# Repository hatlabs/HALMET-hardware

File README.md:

# Hat Labs Marine Engine/Tank Interface

This repository contains the Hat Labs Marine Engine/Tank Interface (HALMET) hardware design. HALMET is a powerful microcontroller development board designed for marine environments with a focus on engine and tank monitoring.

HALMET can be used to easily create different types of sensors and control devices for boats. Use scenarios include:

- RPM sensors
- tank level sensors
- bilge sensors
- Engine alarm sensors
- Engine temperature sensors

Since the board has native WiFi and NMEA 2000 compatible CAN bus connectivity, it can be used to create boards with either Signal K or native NMEA 2000 connectivity (or both!).

## Features

The main design features include:

- Built around ESP32, a powerful 32-bit microcontroller with 4 MB of flash
- Wide-range 6-32 V power input with surge protection
- NMEA 2000 compatible CAN interface (4-pin pluggable terminal block screw connector)
- 4 analog inputs with 0-32V input range and 16-bit resolution (2-pin pluggable terminal block screw connectors)
- 4 digital inputs with -32-32V input range, Schmitt triggered logic level threshold at 1.5V (2-pin pluggable terminal block screw connectors)
- 1-Wire interface (3-pin 2.54 mm header)
- I2C interface with both a SparkFun Qwiic connector and a 4-pin 2.54 mm header
- USB interface for programming and serial communication (USB Micro B)
- All above interfaces with proper electromagnetic compatibilty (EMC) design -- the device won't interfere with navigational devices or radio equipment
- All available general-purpose input/output (GPIO) pins broken out to a separate header
- Board designed to fit low-cost waterproof 100x68x50 mm enclosures

Rendering of a version 1.0.0 board:

<!--
Front side.

Back side.

-->

## Getting HALMET

HALMET will be available for purchase at the [Hat Labs web store](https://shop.hatlabs.fi/).

## Documentation

HALMET documentation will be available at the [project GitHub Pages](https://docs.hatlabs.fi/halmet/).

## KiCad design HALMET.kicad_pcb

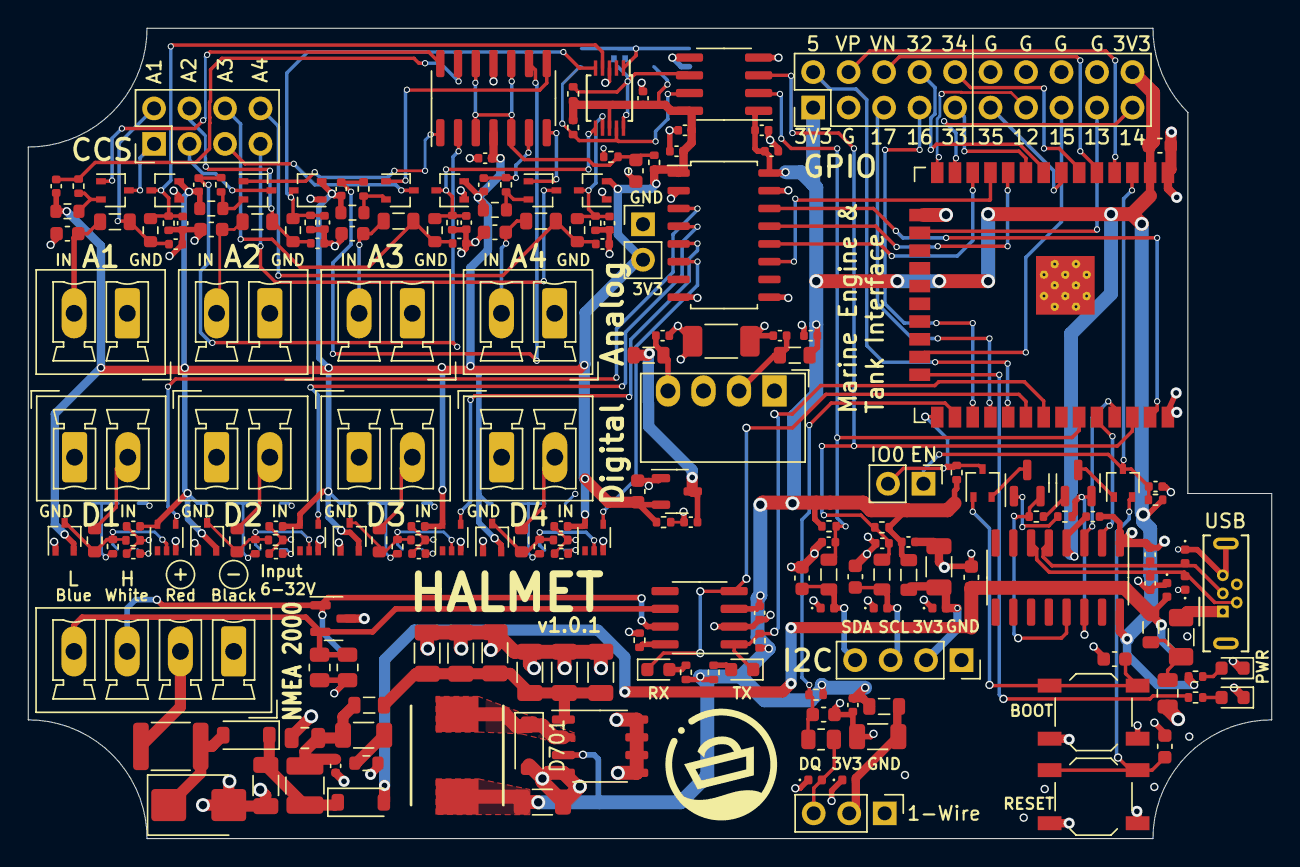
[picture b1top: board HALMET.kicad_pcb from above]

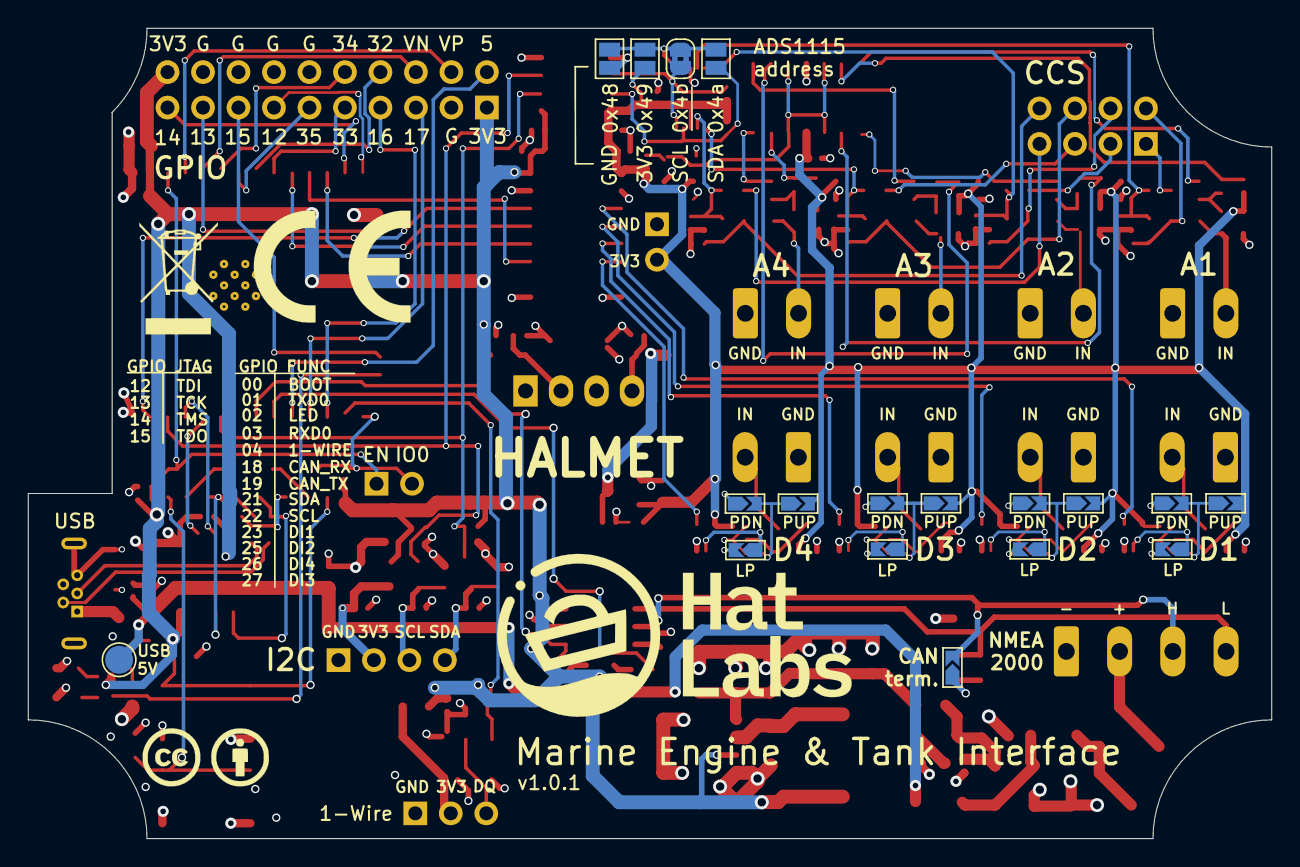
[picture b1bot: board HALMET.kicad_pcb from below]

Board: 4 copper layers, 89.0 x 58.0 mm, 222 parts (21 on the bottom side), 119 nets.

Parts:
C202: 22uF; C_0603_1608Metric
C203: 1uF; C_0402_1005Metric
C304: 47uF/6.3V; C_1206_3216Metric
C402: 4.7uF/16V; C_0603_1608Metric
C403, C404: 10pF/50V; C_0402_1005Metric
C501, C502: 100nF/50V; C_0603_1608Metric
C503, C715: 1uF/50V; C_0805_2012Metric
C601, C604, C612, C614, C705, C706: 33pF/50V; C_0603_1608Metric
C602, C606, C607, C608, C609, C610, C624, C901, C1113, C1114, C1115, C1116, C1204, C1205, C1206, C1207: 100nF; C_0402_1005Metric
C603, C605, C613, C615, C702, C703: 33pF; C_0402_1005Metric
C611: 68nF; C_0603_1608Metric
C620, C621, C622, C623: 10nF; C_0402_1005Metric
C701, C801: 10uF; C_0402_1005Metric
C704, C707, C708, C709, C710, C711, C712, C714, C803: 10uF/50V; C_1206_3216Metric
C713: 4.7nF/50V; C_0402_1005Metric
C716: 4.7uF/50V; C_1206_3216Metric
C802: 1nF/50V; C_0603_1608Metric
C1101, C1102, C1103, C1112: 3.3nF; C_0402_1005Metric
C1104, C1105, C1106, C1107: 220pF; R_0402_1005Metric
C1201, C1202, C1208, C1210: 4.7uF; C_0402_1005Metric
C1203: 10uF/10V; C_0603_1608Metric
C1209: 220pF/2kV; C_1808_4520Metric
D201, D303, D701: B5819W; D_SOD-123
D301: SMBJ33CA; D_SMB
D401, D402, D403, D503, D504, D903, D904, D905: ESD5451N; D_0402_1005Metric
D501: BLUE LED; LED_0603_1608Metric
D502: RED LED; LED_0603_1608Metric
D603, D604, D605, D611, D1103, D1104, D1105, D1113: BAT54S; SOT-323_SC-70
D801: SM24CANB; SOT-23
D1001, D1002: GREEN LED; LED_0603_1608Metric
D1101, D1102: BAT54A; SOT-323_SC-70
F301: mSMD050-60V; Fuse_1812_4532Metric
F401: BSMD1206-100-6V; Fuse_1206_3216Metric
FB401, FB701, FB704, FB801: GZ2012D601TF; L_0805_2012Metric
FB601, FB602, FB603, FB604, FB702, FB703: GZ2012D101TF; L_0805_2012Metric
G601: CC-BY; cc-by_5mm
G602: CE-logo; CE-Logo_11.2x8mm_SilkScreen
G605: HL-Logo; Hat_Labs_25.4mm
G701: HL-Pictogram; HaL_picto_8mm
H1001, H1002: MountingHole; MountingSlot_3.2mm_M3_Unplated
J201: GPIO; PinHeader_2x10_P2.54mm_Vertical
J203: Conn_01x01; TestPoint_Pad_D2.0mm
J302, J1201: Conn_01x02; PinHeader_1x02_P2.54mm_Vertical
J401: USB_B_Micro; USB_Micro-B_Wuerth_614105150721_Vertical
J602: Conn_02x04_Odd_Even; PinHeader_2x04_P2.54mm_Vertical
J604, J605, J606, J607, J1103, J1104, J1105, J1106: Conn_01x02; PhoenixContact_MCV_1,5_2-G-3.81_1x02_P3.81mm_Vertical
J702: Conn_01x04; PinSocket_1x04_P2.54mm_Vertical
J801: Conn_01x03; PinHeader_1x03_P2.54mm_Vertical
J802: Conn_01x04; PhoenixContact_MCV_1,5_4-G-3.81_1x04_P3.81mm_Vertical
JP601, JP1101, JP1102, JP1103, JP1104, JP1105, JP1106, JP1107, JP1108, JP1109, JP1110, JP1111, JP1112: SolderJumper_2_Open; SolderJumper-2_P1.3mm_Open_TrianglePad_Narrow
JP602, JP604, JP605: Open; SolderJumper-2_P1.3mm_Open_Pad1.0x1.5mm
JP603: Bridged; SolderJumper-2_P1.3mm_Bridged2Bar_RoundedPad1.0x1.5mm
L301: SMMS0650-470M; SMMS0650-1R0M
L701: NLCV32T-100K-EFR; L_1210_3225Metric
L1201, L1202: CMH201209B4R7MT; L_0805_2012Metric
PS1201: B0305S-1WR3; Converter_DCDC_Murata_MEE1SxxxxSC_THT
Q401, Q402: S8050; SOT-23
Q601, Q602, Q603, Q604: S9015; SOT-323_SC-70
R201, R213, R401, R402, R503, R612, R1103: 10k; R_0402_1005Metric
R501, R502, R701, R702, R1202, R1203: 2k; R_0402_1005Metric
R601, R602: 240R; R_0805_2012Metric
R603, R604, R605, R606, R611: 1k; R_0402_1005Metric
R607, R608, R609, R610: 30; R_0603_1608Metric
R613, R614, R616, R618, R1101, R1102, R1104, R1105: 20k; R_0603_1608Metric
R615, R617, R619, R621, R801: 2.2k; R_0402_1005Metric
R703: 4.7R; R_0603_1608Metric
R802: 100R; R_0805_2012Metric
R1001, R1002: 1.5k; R_0402_1005Metric
R1106, R1107, R1108, R1109: 100k; R_0402_1005Metric
R1201: 330R; R_0402_1005Metric
SW501, SW502: SW_Push; SW_SPST_TL3342
U201: ESP32-WROOM-32E-N16; ESP32-WROOM-32
U202: XL1509-3.3; SOP-8_3.9x4.9mm_P1.27mm
U401: CH340C; SOIC-16_3.9x9.9mm_P1.27mm
U501: SN65HVD230DR; SOIC-8_3.9x4.9mm_P1.27mm
U601: LMV324; SOIC-14_3.9x8.7mm_P1.27mm
U602: ADS1115IDGS; TSSOP-10_3x3mm_P0.5mm
U1101, U1102, U1103, U1104: 74LVC1G17; SOT-353_SC-70-5
U1201: π140U30; SOIC-16_4.55x10.3mm_P1.27mm
U1202: ISO1540; SOIC-8_3.9x4.9mm_P1.27mm
U1203: XC6206P332MR; SOT-23-3

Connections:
+3.3V: C202.2, C304.1, C602.1, C701.1, C801.1, C901.1, C1201.1, C1206.1, C1207.1, FB701.2, FB801.2, J201.1, J201.20, L301.2, L1201.1, R201.1, R213.1, R502.1, R701.2, R702.2, R801.2, R1001.1, R1002.1, R1103.1, U201.2 (VDD), U202.3 (FB), U401.4 (V3), U401.16 (VCC), U501.3 (VCC), U1201.16 (VDD2), U1202.1 (VCC1)
+3.3V_1: C606.2, C607.2, C608.2, C609.2, C610.1, C624.1, C1113.1, C1114.1, C1115.1, C1116.1, C1203.1, C1204.1, C1205.1, D603.2 (K), D604.2 (K), D605.2 (K), D611.2 (K), D1103.2 (K), D1104.2 (K), D1105.2 (K), D1113.2 (K), J1201.2, JP602.2 (B), JP1106.2 (B), JP1107.2 (B), JP1109.2 (B), JP1111.2 (B), R607.1, R608.1, R609.1, R610.1, R611.1, R1201.1, R1202.2, R1203.2, U601.4 (V+), U602.8 (VDD), U1101.5 (VCC), U1102.5 (VCC), U1103.5 (VCC), U1104.5 (VCC), U1201.1 (VDD1), U1202.8 (VCC2), U1203.2 (VOUT)
/Analog input/ADC_A1: C620.1, D611.3 (COM), R613.1, R621.2, U602.4 (AIN0)
/Analog input/ADC_A2: C621.1, D603.3 (COM), R614.1, R615.2, U602.5 (AIN1)
/Analog input/ADC_A3: C622.1, D604.3 (COM), R616.1, R617.2, U602.6 (AIN2)
/Analog input/ADC_A4: C623.1, D605.3 (COM), R618.1, R619.2, U602.7 (AIN3)
/Analog input/ADDR: JP602.1 (A), JP603.1 (A), JP604.1 (A), JP605.1 (A), U602.1 (ADDR)
/Analog input/INA1: C601.1, FB601.1, J606.2
/Analog input/INA2: C604.1, FB602.1, J604.2
/Analog input/INA3: C612.1, FB603.1, J605.2
/Analog input/INA4: C614.1, FB604.1, J607.2
/Analog input/INFA1: C603.1, FB601.2, J602.2, R613.2
/Analog input/INFA2: C605.1, FB602.2, J602.4, R614.2
/Analog input/INFA3: C613.1, FB603.2, J602.6, R616.2
/Analog input/INFA4: C615.1, FB604.2, J602.8, R618.2
/Analog input/IoutA1: J602.1, Q601.3 (C)
/Analog input/IoutA2: J602.3, Q602.3 (C)
/Analog input/IoutA3: J602.5, Q603.3 (C)
/Analog input/IoutA4: J602.7, Q604.3 (C)
/Analog input/QBA1: Q601.1 (B), U601.14
/Analog input/QBA2: Q602.1 (B), U601.1
/Analog input/QBA3: Q603.1 (B), U601.8
/Analog input/QBA4: Q604.1 (B), U601.7
/Analog input/SCL: JP603.2 (B), R1203.1, U602.10 (SCL), U1202.6 (SCL2)
/Analog input/SDA: JP604.2 (B), R1202.1, U602.9 (SDA), U1202.7 (SDA2)
/Analog input/Vin: C611.1, R611.2, R612.1, U601.3 (+), U601.5 (+), U601.10 (+), U601.12 (+)
/BOOT_AUTO: D1101.2, Q402.3 (C)
/BOOT_KEY: C501.1, D1101.1, SW501.2
/CAN_H: D801.1 (A1), J802.3, JP601.2 (B), U501.7 (CANH)
/CAN_L: D801.2 (A2), J802.4, R601.2, R602.2, U501.6 (CANL)
/CAN_RX: D1001.1 (K), U201.30 (IO18), U501.4 (R)
/CAN_TX: D1002.1 (K), R213.2, U201.31 (IO19), U501.1 (D)
/DI1: U201.37 (IO23), U1201.14 (VOA)
/DI2: U201.10 (IO25), U1201.13 (VOB)
/DI3: U201.12 (IO27), U1201.12 (VOC)
/DI4: U201.11 (IO26), U1201.11 (VOD)
/DQ: C802.1, R801.1, R802.1, U201.26 (IO4)
/Digital input/DigIn1: U1101.4, U1201.3 (VIA)
/Digital input/DigIn2: U1102.4, U1201.4 (VIB)
/Digital input/DigIn3: U1103.4, U1201.5 (VIC)
/Digital input/DigIn4: U1104.4, U1201.6 (VID)
/Digital input/In1: J1103.2, R1101.2
/Digital input/In2: J1104.2, R1102.2
/Digital input/In3: J1105.2, R1104.2
/Digital input/In4: J1106.2, R1105.2
/Digital input/Inp1: C1104.1, D1113.3 (COM), JP1101.1 (A), R1101.1, R1106.2, U1101.2
/Digital input/Inp2: C1105.1, D1103.3 (COM), JP1102.1 (A), R1102.1, R1107.2, U1102.2
/Digital input/Inp3: C1106.1, D1104.3 (COM), JP1103.1 (A), R1104.1, R1108.2, U1103.2
/Digital input/Inp4: C1107.1, D1105.3 (COM), JP1104.1 (A), R1105.1, R1109.2, U1104.2
/ESP32/EN: C203.1, D1102.3, J302.1, R201.2, U201.3 (EN)
/ESP32/IO0: D1101.3, J302.2, R1103.2, U201.25 (IO0)
/ESP32/IO5: J201.2, U201.29 (IO5)
/ESP32/IO16: J201.7, U201.27 (IO16)
/ESP32/IO17: J201.5, U201.28 (IO17)
/ESP32/IO32: J201.8, U201.8 (IO32)
/ESP32/IO33: J201.9, U201.9 (IO33)
/ESP32/IO34: J201.10, U201.6 (IO34)
/ESP32/IO35: J201.11, U201.7 (IO35)
/ESP32/SENSOR_VN: J201.6, U201.5 (SENSOR_VN)
/ESP32/SENSOR_VP: J201.4, U201.4 (SENSOR_VP)
/ESP32/TCK: J201.17, U201.16 (IO13)
/ESP32/TDI: J201.13, U201.14 (IO12)
/ESP32/TDO: J201.15, U201.23 (IO15)
/ESP32/TMS: J201.19, U201.13 (IO14)
/I2C/I2C_3V3: C704.1, D403.2 (A2), FB701.1, J702.2
/I2C/SCL_CONN: C706.1, D402.2 (A2), FB703.1, J702.3
/I2C/SDA_CONN: C705.1, D401.2 (A2), FB702.1, J702.4
/Isolation barrier/5V_unreg: C1202.1, L1202.2, U1203.3 (VIN)
/Isolation barrier/Vin_: C1208.1, L1201.2, PS1201.2 (+Vin)
/Isolation barrier/Vout_: C1210.1, L1202.1, PS1201.4 (+Vout)
/LED: R501.1, U201.24 (IO2)
/Onewire/DQ_CONN: D503.2 (A2), J801.3, R802.2
/Onewire/Onewire_3V3: C803.1, D504.2 (A2), FB801.1, J801.2
/Power input/CAN_+: F301.2, J802.2
/Power input/IN: C707.1, C708.1, C709.1, C710.1, C711.1, C712.1, FB704.1, U202.1 (IN)
/Power input/SW: D701.1 (K), L301.1, U202.2 (SW)
/Power input/Vin_fused: D301.1 (A1), D303.2 (A), F301.1
/Power input/Vin_protected: C714.2, D201.1 (K), D303.1 (K), L701.1
/RESET_AUTO: D1102.1, Q401.3 (C)
/RESET_KEY: C502.1, D1102.2, SW502.2
/SCL: C703.1, FB703.2, R702.1, U201.36 (IO22), U1202.3 (SCL1)
/SDA: C702.1, FB702.2, R701.1, U201.33 (IO21), U1202.2 (SDA1)
/USB/DTR: Q402.2 (E), R401.1, U401.13 (~DTR)
/USB/RTS: Q401.2 (E), R402.1, U401.14 (~RTS)
/USB/USB_D+: C403.1, D904.2 (A2), J401.3 (D+), U401.5 (UD+)
/USB/USB_D-: C404.1, D905.2 (A2), J401.2 (D-), U401.6 (UD-)
/USB/VBUS: F401.2, J401.1 (VBUS)
/USB_RXD: U201.35 (TXD0/IO1), U401.3 (RXD)
/USB_TXD: U201.34 (RXD0/IO3), U401.2 (TXD)
GND: C202.1, C203.2, C304.2, C402.2, C403.2, C404.2, C501.2, C502.2, C503.2, C602.2, C701.2, C702.2, C703.2, C704.2, C705.2, C706.2, C707.2, C708.2, C709.2, C710.2, C711.2, C712.2, C713.2, C714.1, C715.1, C801.2, C802.2, C803.2, C901.2, C1201.2, C1206.2, C1207.2, C1208.2, C1209.1, D301.2 (A2), D401.1 (A1), D402.1 (A1), D403.1 (A1), D501.1 (K), D502.1 (K), D503.1 (A1), D504.1 (A1), D701.2 (A), D801.3 (common), D903.1 (A1), D904.1 (A1), D905.1 (A1), J201.3, J201.12, J201.14, J201.16, J201.18, J401.5 (GND), J401.6 (Shield), J702.1, J801.1, J802.1, PS1201.1 (-Vin), R503.2, R703.1, SW501.1, SW502.1, U201.1 (GND), U201.15 (GND), U201.38 (GND), U201.39 (GND), U202.4 (~EN), U202.5 (GND), U202.6 (GND), U202.7 (GND), U202.8 (GND), U401.1 (GND), U501.2 (GND), U1201.9 (GND2), U1201.15 (GND2), U1202.4 (GND1)
GND1: C601.2, C603.2, C604.2, C605.2, C610.2, C611.2, C612.2, C613.2, C614.2, C615.2, C620.2, C621.2, C622.2, C623.2, C624.2, C1101.2, C1102.2, C1103.2, C1104.2, C1105.2, C1106.2, C1107.2, C1112.2, C1113.2, C1114.2, C1115.2, C1116.2, C1202.2, C1203.2, C1204.2, C1205.2, C1209.2, C1210.2, D603.1 (A), D604.1 (A), D605.1 (A), D611.1 (A), D1103.1 (A), D1104.1 (A), D1105.1 (A), D1113.1 (A), J604.1, J605.1, J606.1, J607.1, J1103.1, J1104.1, J1105.1, J1106.1, J1201.1, JP605.2 (B), JP1105.1 (A), JP1108.1 (A), JP1110.1 (A), JP1112.1 (A), PS1201.3 (-Vout), R612.2, R615.1, R617.1, R619.1, R621.1, R1201.2, U601.11 (V-), U602.3 (GND), U1101.3 (GND), U1102.3 (GND), U1103.3 (GND), U1104.3 (GND), U1201.2 (GND1), U1201.8 (GND1), U1202.5 (GND2), U1203.1 (GND)
unnamed: C503.1, F401.1, FB401.2
unnamed: C713.1, C715.2, C716.1, FB704.2, L701.2
unnamed: C716.2, R703.2
unnamed: D501.2 (A), R501.2
unnamed: D502.2 (A), R502.2
unnamed: D1001.2 (A), R1001.2
unnamed: D1002.2 (A), R1002.2
unnamed: JP601.1 (A), R601.1, R602.1
unnamed: C1112.1, JP1101.2 (B)
unnamed: C1101.1, JP1102.2 (B)
unnamed: C1102.1, JP1103.2 (B)
unnamed: C1103.1, JP1104.2 (B)
unnamed: JP1105.2 (B), JP1106.1 (A), R1106.1
unnamed: JP1107.1 (A), JP1108.2 (B), R1107.1
unnamed: JP1109.1 (A), JP1110.2 (B), R1108.1
unnamed: JP1111.1 (A), JP1112.2 (B), R1109.1
unnamed: Q401.1 (B), R401.2
unnamed: Q402.1 (B), R402.2
unnamed: Q601.2 (E), R603.1, R607.2
unnamed: Q602.2 (E), R604.1, R608.2
unnamed: Q603.2 (E), R605.1, R609.2
unnamed: Q604.2 (E), R606.1, R610.2
unnamed: R503.1, U501.8 (Rs)
unnamed: C607.1, R604.2, U601.2 (-)
unnamed: C609.1, R606.2, U601.6 (-)
unnamed: C608.1, R605.2, U601.9 (-)
unnamed: C606.1, R603.2, U601.13 (-)
USB_5V: C402.1, D201.2 (A), D903.2 (A2), FB401.1, J203.1

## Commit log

2023-09-19 HALMET redesign
2023-09-19 Substitute parts according to availability
2023-11-28 Implement HALMET v1.0.0 design changes
2023-12-05 Update parts according to availability
2024-01-05 Fix DI4 & DI3 pins
2024-01-18 Version 1.0.1 changes
    - Add a power header to isolated side
    - Fix GPIO silk screen bugs
    - Add labels for isolated I2C pads
    - Bump version to 1.0.1
2025-09-01 Save with a newer KiCad; change parts for availability; fix rotations

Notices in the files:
HALMET.kicad_pcb:
https://creativecommons.org/licenses/by-sa/4.0
HALMET is licensed under CC BY-SA 4.0.
